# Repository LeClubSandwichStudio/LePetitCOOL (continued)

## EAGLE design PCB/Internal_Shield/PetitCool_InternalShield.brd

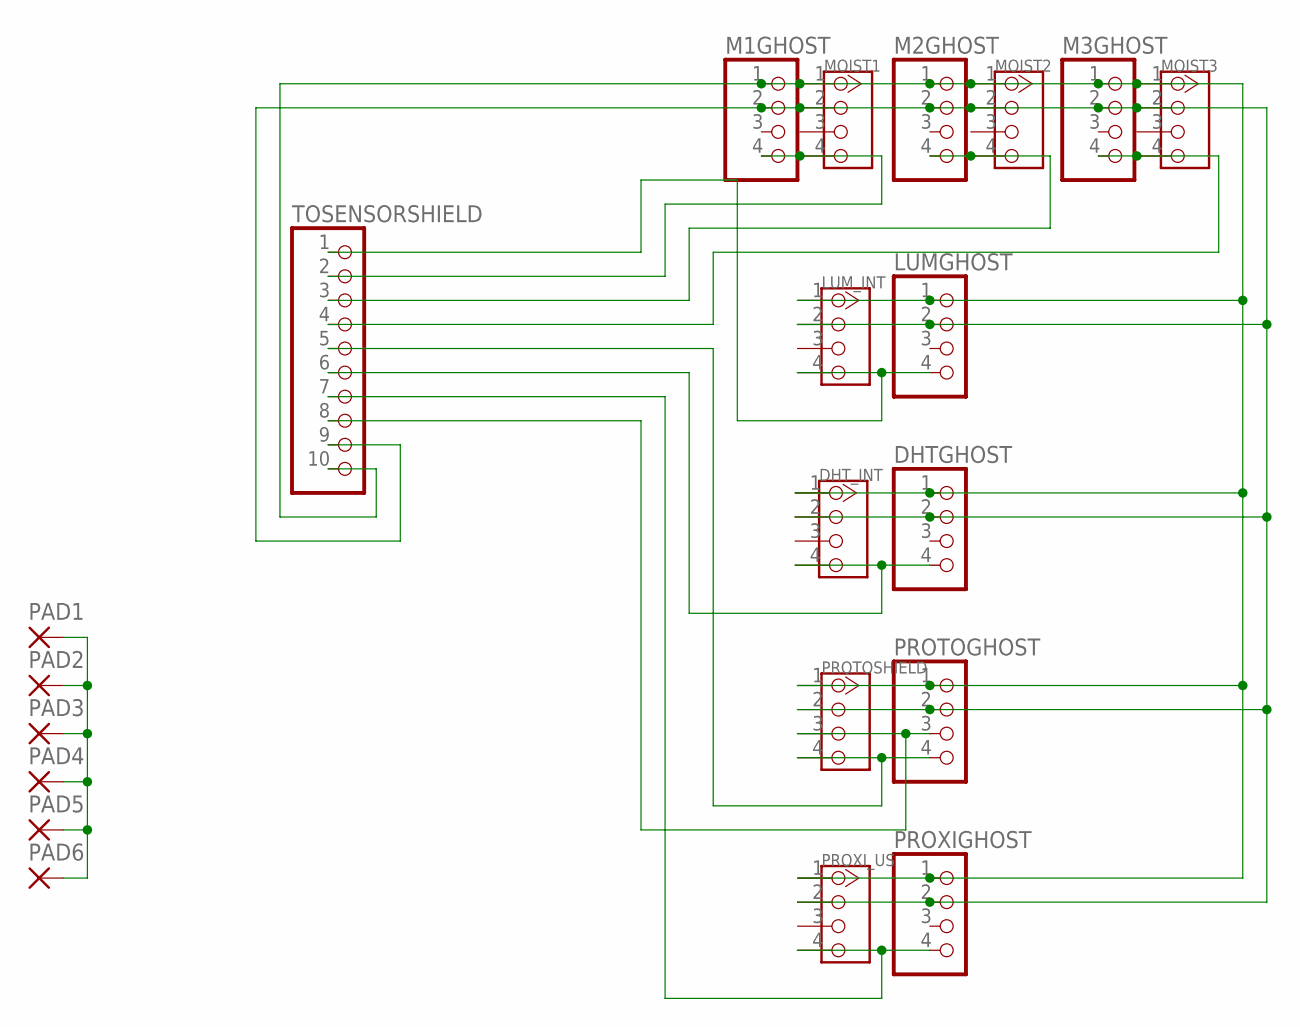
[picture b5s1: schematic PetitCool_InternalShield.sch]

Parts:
DHTGHOST: PINHD-1X4; 1X04
DHT_INT: TWIG-4P-2.0-2.0; 4P-2.0
LUMGHOST: PINHD-1X4; 1X04
LUM_INT: TWIG-4P-2.0-2.0; 4P-2.0
M1GHOST, M2GHOST, M3GHOST: PINHD-1X4; 1X04
MOIST1, MOIST2, MOIST3: TWIG-4P-2.0-2.0; 4P-2.0
PAD1, PAD2, PAD3, PAD4, PAD5, PAD6: 2,15/1,0
PROTOGHOST: PINHD-1X4; 1X04
PROTOSHIELD: TWIG-4P-2.0-2.0; 4P-2.0
PROXIGHOST: PINHD-1X4; 1X04
PROXI_US: TWIG-4P-2.0-2.0; 4P-2.0
TOSENSORSHIELD: PINHD-1X10; 1X10

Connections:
+5V: DHTGHOST.2, DHT_INT.2, LUMGHOST.2, LUM_INT.2, M1GHOST.2, M2GHOST.2, M3GHOST.2, MOIST1.2, MOIST2.2, MOIST3.2, PROTOGHOST.2, PROTOSHIELD.2, PROXIGHOST.2, PROXI_US.2, TOSENSORSHIELD.9
DHT_INT(D36): DHTGHOST.4, DHT_INT.4, TOSENSORSHIELD.6
GND_5V: DHTGHOST.1, DHT_INT.1, LUMGHOST.1, LUM_INT.1, M1GHOST.1, M2GHOST.1, M3GHOST.1, MOIST1.1, MOIST2.1, MOIST3.1, PAD1.1, PAD2.1, PAD3.1, PAD4.1, PAD5.1, PAD6.1, PROTOGHOST.1, PROTOSHIELD.1, PROXIGHOST.1, PROXI_US.1, TOSENSORSHIELD.10
LUM_INT(A10): LUMGHOST.4, LUM_INT.4, TOSENSORSHIELD.1
MOIST1(A11): M1GHOST.4, MOIST1.4, TOSENSORSHIELD.2
MOIST2(A12): M2GHOST.4, MOIST2.4, TOSENSORSHIELD.3
MOIST3(A13): M3GHOST.4, MOIST3.4, TOSENSORSHIELD.4
PROTO(A14): PROTOGHOST.4, PROTOSHIELD.4, TOSENSORSHIELD.5
PROTO(D44): PROTOGHOST.3, PROTOSHIELD.3, TOSENSORSHIELD.8
PROXI_US(D38): PROXIGHOST.4, PROXI_US.4, TOSENSORSHIELD.7

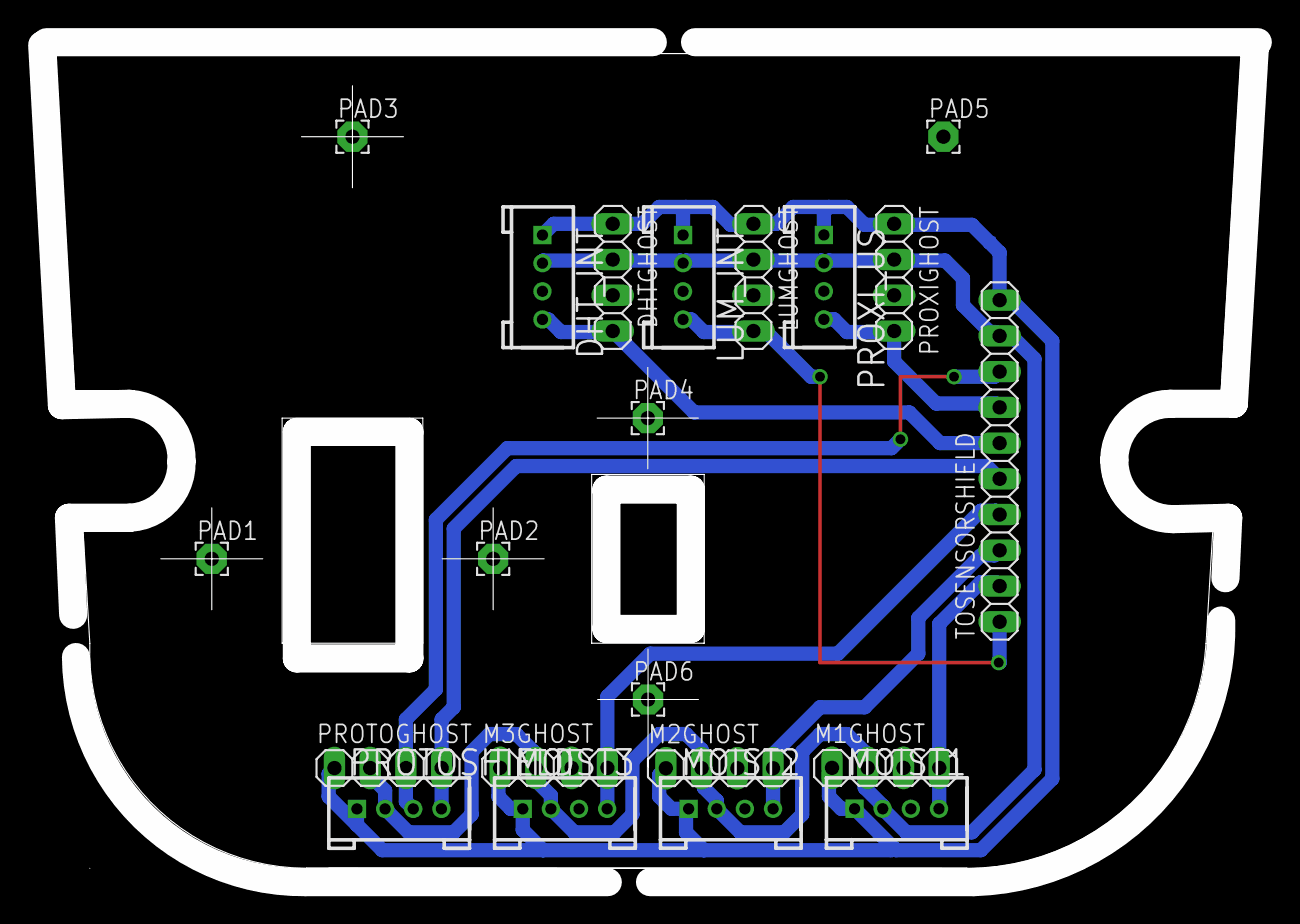
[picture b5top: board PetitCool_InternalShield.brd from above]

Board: 2 copper layers, 86.4 x 59.7 mm, 21 parts (0 on the bottom side), 10 nets.

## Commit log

2015-10-07 Create PCB
2015-10-07 Create PCB
    Here is all you need to product your own COOL circuits !!!
2015-10-07 Create Le Petit COOL
    Here is all you need to product your own COOL wooden parts
2015-10-07 COOL Libraries
2015-11-18 Le Petit Cool : Arduino Sketch V1.0
2015-11-18 Le Petit Cool : Global Definitions V1.0
2015-11-18 Le Petit Cool : Application Intelligence V1.0
2015-11-18 Le Petit Cool : Machine Intelligence V1.0
2015-11-18 Le Petit Cool : RTC Library V1.0
2015-11-18 Le Petit Cool : Temperature & Humidity Sensing Library V1.0
2015-11-18 Le Petit Cool : Luminosity Sensing Library V1.0
2015-11-18 Le Petit Cool : Moisture Sensing Library V1.0
2015-11-18 Le Petit Cool : Water Level Sensing Library V1.0
2015-11-18 Le Petit Cool : Display System Library V1.0
2015-11-18 Le Petit Cool : Ventilation System Library V1.0
2015-11-18 Le Petit Cool : Light System Library V1.0
2015-11-18 Le Petit Cool : Water Management System Library V1.0
2015-11-18 Le Petit Cool - Internal Shield V1.0
2015-11-18 Le Petit Cool - Led Shield V1.0
2015-11-18 Le Petit Cool - Main Shield V1.0
2015-11-18 Le Petit Cool - Power Shield V1.0
2015-11-18 Le Petit Cool - Sensor Shield V1.0
